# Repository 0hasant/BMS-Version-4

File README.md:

# Solar Team Solaris BMS Version 4

BQ76952-based BMS (up to 16S per board) with an STM32F103C8 host, isolated CAN,
external cell balancing and contactor control.

**System:** the 26S battery pack uses **two BMS boards**. Contactor coil current
is about 0.4 A. Balancing is enabled by an external button (J4 opto input).

**Active branch:** `v4.02` (the ordered board, Gerbers in `Hardware/All_Gerber/Gerber v4.02.zip`).

**Present focus:** make the firmware stable on the board that already works
(v4.013) before the v4.02 board arrives.

---

## Firmware (Software/BMSv4_Main_Code)

### Done
- [x] SPI driver with CRC check and retries on every frame (`bq76952.c`)
- [x] CONFIG_UPDATE wait checks the correct bit (Battery Status bit 0, `CFGUPDATE`)
- [x] All RAM settings written in one CONFIG_UPDATE session and read back to verify
- [x] BQ76952 reset detected (POR flag) and configuration re-applied automatically
- [x] MCU reset button (S2) also resets the BQ76952 (`BQ_RESET_ON_BOOT`)
- [x] Independent watchdog (IWDG, ~2 s, frozen while debugging)
- [x] Safety Status A/B/C, Battery Status and Alarm Status read every loop
- [x] Stack voltage as `uint32_t` (a full 16S pack is above 65.5 V)
- [x] Communication health counters in `BQ_Health` (watch in debugger)
- [x] Cell count selectable with `BMS_CELL_CONFIG` in `bq76952.h` (7 = 7S bench test, 13, 16).
      7S bench wiring: cells 1-7 on VC1-VC7, VC8..VC16 shorted to the top of cell 7 (`BMS_7S_TOP_ON_VC16 0`).
      Wiring check in the debugger: `BQ_Input_mV[16]` and `Stack_Diff_mV` (should be about 0)
- [x] CC Gain / Capacity Gain written from `BQ_SHUNT_MOHM`: current register is real mA (+/-32.7 A range).
      Calibrate by adjusting `BQ_SHUNT_MOHM` against a reference meter

### To do (on the working board)
- [ ] Protection setup: COV/CUV for the DMEGC INR45E cells, enable CUV, OCC/OCD1/OCD2/SCD
      thresholds for the 2 mOhm shunt (default SCD = 10 mV = only 5 A!), OTC/OTD
- [ ] Current: fine-tune `BQ_SHUNT_MOHM` with a current source, Board Offset (0x91C8) for the zero reading,
      10 mA user units if more than 32 A must be read
- [ ] Disable the charge pump (CP1 is tied to BAT, saves ~200 uA)
- [ ] Balancing: production `BALANCE_MIN_VOLTAGE_MV = 3900`, real temperature limits,
      `BALANCE_MAX_CELLS` chosen for heat (see Hardware notes)

### To do (for the v4.02 board, after it arrives)
- [ ] Fix `.ioc` before regenerating code:
  - PB10 = BMS number input (pull-down R31). PB11 = **contactor output** (rework below)
  - Mux select lines: PB15 = S0, PB14 = S1, PB13 = S2, PB12 = S3 (the `.ioc` has them reversed)
  - Remove PB8 output and I2C1 (PB8/PB7 are tied to SPI SCLK/MISO through R1/R2)
  - HSE = crystal (Y1, 16 MHz), not external clock; then 72 MHz SYSCLK
  - PA8 = balance-enable opto input (pull-up R30), PA0 = ADC for the thermistor mux
  - CAN at the bitrate used by the car
- [ ] Contactor logic on PB11: ON only when configured, no safety fault, SPI healthy;
      OFF on any fault. Watchdog reset -> pin floats -> R32 pulls it low -> contactor OFF
- [ ] 13S per board: set `BMS_CELL_CONFIG 13` (`0x8FFF`, unused VC13-VC15 shorted to VC12);
      board number from PB10
- [ ] Cell temperature reading through the CD74HC4067 mux
- [ ] CAN messages
- [ ] Balance-enable button (J4) with debounce

---

## Hardware

### v4.02 (ordered) - fixes before / during assembly
- [ ] **PS1:** fit **1S4E_0505S1U** (5 V in). The BOM part 1S4E_1505S1U is the 15 V input version -> CAN would be dead
- [ ] **F1:** 250 mA fuse blows when the top cell balances (~0.42 A). Use 1 A, 2410 size
      (e.g. Reomax SET1100 1 A 125 V time-lag, in stock at Özdisan). The 2410 body (6.1 mm) is
      longer than the 2010 footprint, solder carefully
- [ ] **Contactor drive (DDSG can't drive the PhotoMOS LEDs from REG18):**
  1. Bottom side: cut the short trace from the via in R10 pad 2 (89.5, 83.25) to the via at (95.25, 87.03)
  2. Wire SW1 pin 2 (PB11) to R28 pad 1 (R28/R29 LED node)
  3. Do **not** close SW1 position 1-2 (it would force the contactor on). Better: leave SW1 out and
     bridge pads 3-4 for BMS #2 (PB10 high)
  4. R10 can stay unfitted. Keep R32 (pull-down = contactor off during reset)
- [ ] **R1/R2:** leave unfitted (reserved for future I2C work)
- [ ] **VDDA:** add 100 nF + 1 uF from TP5 to GND (no decoupling on the board)
- [ ] **Ground, lower board (carries pack current through the shunt):** wire GND to TP2 (-Batt_In,
      battery side of the shunt) and **remove R43**. Never fit both, or pack current flows in the cell-0 sense wire
- [ ] **Ground, upper board (no pack current):** keep R43 = 0 R, tie TP2 and TP3 to GND so SRP/SRN do not float
- [x] Balance resistors changed to **22 R, 2 W, 2512** (HP122WJ0220T4E) in schematic and PCB: ~0.19 A and
      ~0.8 W each at 4.2 V (10 R was ~1.7 W each). Same footprint, BOM change only.
      Özdisan has it at 0 stock today (Request Price & Stock); any 22 R 2 W 2512 fits
- [ ] C27 (CAN split termination) is 10 pF, should be ~4.7 nF
- [x] BOM regenerated from the current schematic: `Hardware/BMS_V4/BOM/BMS_V4.02_BOM.xlsx` (and `.csv`), see below

### BOM
`Hardware/BMS_V4/BOM/BMS_V4.02_BOM.xlsx` - one line per part number, with Özdisan link, stock, price (TRY, tax
included, at MOQ, checked 2026-10-13) and a "Boards to build" cell that updates the quantities to buy. A second
table lists the off-board parts (mating plugs for J1-J5, jumpers for J7/J8). The `.csv` is the same list as plain text.
`Docs/Listeler/BMS_V4.013.xlsx` and `Hardware/BMS_V4/BMS_V4.csv` are old (v4.013 references), do not order from them.

Not in stock at Özdisan on 2026-10-13 (order elsewhere or "Request Price & Stock"): BQ76952 (U1), CD74HC4067 (U6),
BAT46W (D1), 22R 2W 2512 (balance resistors), NTC TH1-TH3, 10k 1% (R33), 0R (R43), 30pF (C24/C25, 47pF is in stock
if you want to change), 56pF (C33), 1206 caps C1 and C29, 3.3nF 2kV disc (C26), J5 header, J6 box header,
PS1 (not sold by Özdisan; RECOM RFM-0505S is a candidate, check pinout first). C35 (TDK 10uF 50V) has only 9 left.

### Component naming in the schematic
Every symbol now follows the same rule; the full part number is in hidden fields
(`MPN`, `Manufacturer`, `Supplier`, `Supplier Link`), visible in the symbol properties and in the BOM.

| Part type | Value shows | Example |
|---|---|---|
| Resistor | resistance, power only if >= 1 W, tolerance only where it matters | `4.7k`, `22R 2W`, `10k 1%` |
| Capacitor | capacitance + voltage | `100nF 50V`, `3.3nF 2kV` |
| Inductor / crystal / fuse | main value | `220uH`, `16MHz`, `1A slow` |
| IC, diode, transistor | short part name | `BQ76952`, `SI1050X`, `BAT54C` |
| Connector / switch | what it connects or does | `Cells 0-9`, `CAN`, `BMS ID`, `MCU reset` |

R1 and R2 are marked DNP (do not populate). The PCB Value fields were synced to the schematic
(this also fixes Q1-Q16, which showed RQ6E080AJ on the PCB).

Reference designators kept as they are on v4.02 so they match the ordered board's silkscreen.
For v4.03 rename: C36/C37 (PhotoMOS relays) -> K1/K2, LED1 -> D36, IC1/IC2 -> U7/U8.

### Next revision (v4.03) wish list
- [ ] Power REGIN from +5V_Main (BREG tied to REGIN, 1 uF at REGIN, 1 uF at REG1) and enable REG1 = 3.3 V:
      MISO becomes 3.3 V logic (`MISO_REG1` + SWAP_TO_SPI), and DDSG/DCHG can drive real loads.
      Not practical as a bodge on v4.02: pins 36/37 are tied to GND by traces that meet under the chip body
- [ ] **BQ reset button is wired wrong.** In the "bq76952 reset" block, R11 and C9 land on the S1 NO/GND side, so
      pressing S1 only shorts the R12 node (3.3 V via 4.7 k) to GND and RST_SHUT never goes high.
      Fix: +3.3V -> S1 -> R12 (1 k) -> RST_SHUT; RST_SHUT -> R11 (10 k, was 100 R) -> GND; C9 100 nF RST_SHUT -> GND.
      Short press = reset, held > 1 s = SHUTDOWN (the TS2 thermistor wakes it again). Optionally also an STM32 pin.
      On v4.02: use S2; the firmware sends RESET() to the BQ at every MCU boot
- [ ] Direct GND star point at the battery side of the shunt, VC0 through R/C to it
- [ ] Separate VC16 sense wire from the fused power wire (fuse drop shows up in cell 16)
- [ ] Balance-enable input: R27 sized for the button supply voltage (5 V needs ~1 k)
- [ ] Contactor wiring for two boards in series (flyback diode only once, across the coil)
- [ ] MOSI bottom link is a graphic line with a net; convert to a real track

---

## Repository organisation

- `main` is far behind `v4.02`: merge `v4.02` into `main` once the board is verified
- Remove `Hardware/BMS_V4/untitled.kicad_sch` (not in the hierarchy, old flat schematic)
- Lock files (`*.lck`), `fp-info-cache` and auto-save files are now ignored; don't commit them
- `Hardware/Porduciton Outputs/` -> rename to `Production Outputs`; `report.txt` still points to v4.013
- Keep one BOM file generated from the current schematic, next to the Gerbers of the same version
- Tag each ordered board, e.g. `hw-v4.02` on the commit the Gerbers came from

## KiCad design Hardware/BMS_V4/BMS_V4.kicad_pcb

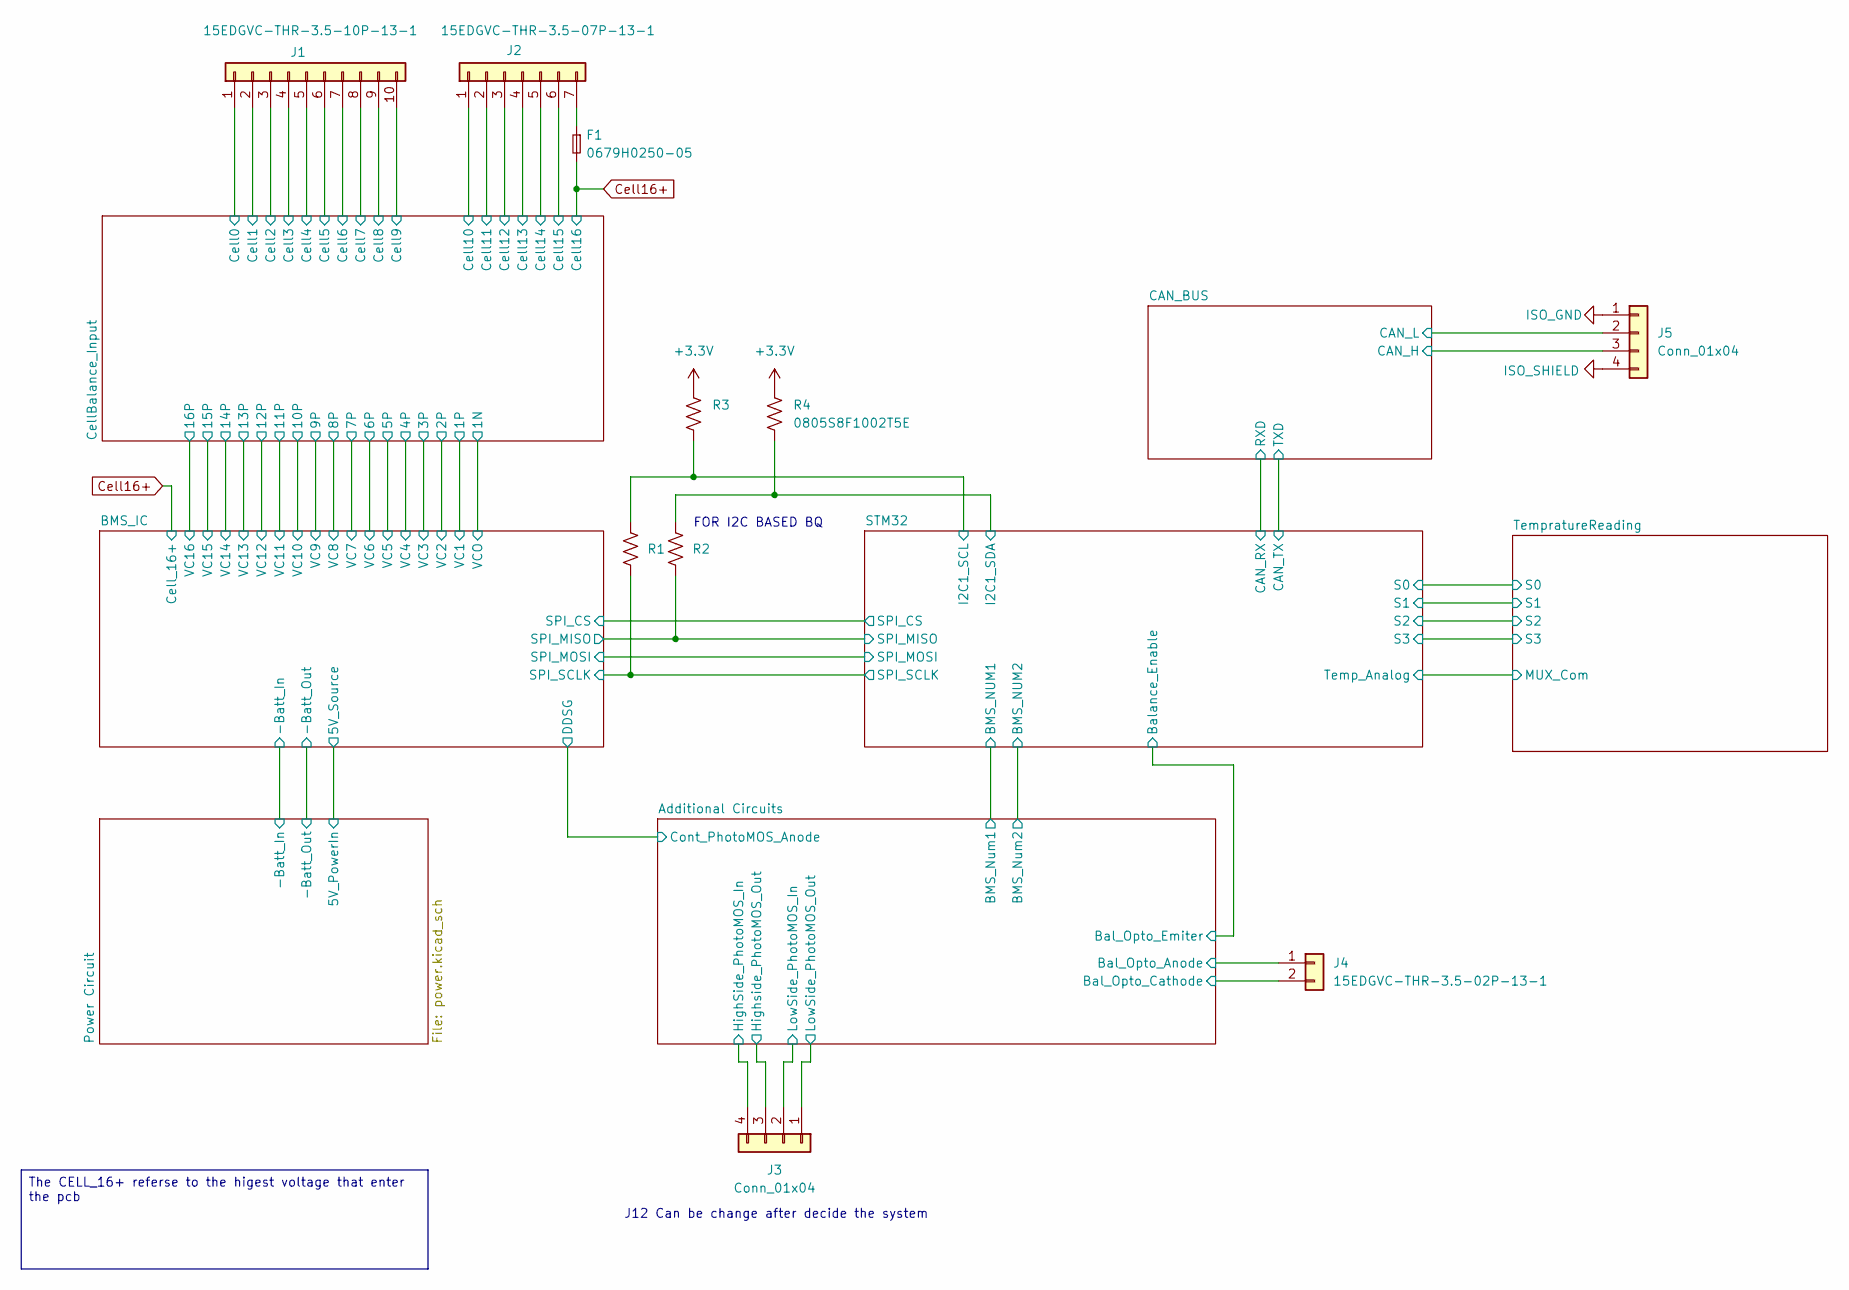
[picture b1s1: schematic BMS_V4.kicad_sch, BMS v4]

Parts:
F1: 0679H0250-05; Fuse_2010_5025Metric_Pad1.52x2.65mm_HandSolder
J1: 15EDGVC-THR-3.5-10P-13-1; PhoenixContact_MCV_1,5_10-G-3.5_1x10_P3.50mm_Vertical
J2: 15EDGVC-THR-3.5-07P-13-1; PhoenixContact_MCV_1,5_7-G-3.5_1x07_P3.50mm_Vertical
J3: Conn_01x04; Wago_734-134_1x04_P3.50mm_Vertical
J4: 15EDGVC-THR-3.5-02P-13-1; Wago_734-132_1x02_P3.50mm_Vertical
J5: Conn_01x04; PhoenixContact_MSTBVA_2,5_4-G-5,08_1x04_P5.08mm_Vertical
R1, R2: 0805S8F0000TDE; R_0805_2012Metric_Pad1.20x1.40mm_HandSolder
R3, R4: 0805S8F1002T5E; R_0805_2012Metric_Pad1.20x1.40mm_HandSolder

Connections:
+3.3V: R3.1, R4.2; also elsewhere on the board
/Additional Circuits/Bal_Opto_Anode: J4.1; also elsewhere on the board
/Additional Circuits/Bal_Opto_Cathode: J4.2; also elsewhere on the board
/Additional Circuits/HighSide_PhotoMOS_In: J3.4; also elsewhere on the board
/Additional Circuits/Highside_PhotoMOS_Out: J3.3; also elsewhere on the board
/Additional Circuits/LowSide_PhotoMOS_In: J3.2; also elsewhere on the board
/Additional Circuits/LowSide_PhotoMOS_Out: J3.1; also elsewhere on the board
/BMS_IC/SPI_MISO: R2.2; also elsewhere on the board
/BMS_IC/SPI_SCLK: R1.2; also elsewhere on the board
/CAN_BUS/CAN_H: J5.3; also elsewhere on the board
/CAN_BUS/CAN_L: J5.2; also elsewhere on the board
/CellBalance_Input/Cell0: J1.1; also elsewhere on the board
/CellBalance_Input/Cell1: J1.2; also elsewhere on the board
/CellBalance_Input/Cell2: J1.3; also elsewhere on the board
/CellBalance_Input/Cell3: J1.4; also elsewhere on the board
/CellBalance_Input/Cell4: J1.5; also elsewhere on the board
/CellBalance_Input/Cell5: J1.6; also elsewhere on the board
/CellBalance_Input/Cell6: J1.7; also elsewhere on the board
/CellBalance_Input/Cell7: J1.8; also elsewhere on the board
/CellBalance_Input/Cell8: J1.9; also elsewhere on the board
/CellBalance_Input/Cell9: J1.10; also elsewhere on the board
/CellBalance_Input/Cell10: J2.1; also elsewhere on the board
/CellBalance_Input/Cell11: J2.2; also elsewhere on the board
/CellBalance_Input/Cell12: J2.3; also elsewhere on the board
/CellBalance_Input/Cell13: J2.4; also elsewhere on the board
/CellBalance_Input/Cell14: J2.5; also elsewhere on the board
/CellBalance_Input/Cell15: J2.6; also elsewhere on the board
/STM32/I2C1_SCL: R1.1, R3.2; also elsewhere on the board
/STM32/I2C1_SDA: R2.1, R4.1; also elsewhere on the board
Cell16+: F1.2; also elsewhere on the board
ISO_GND: J5.1; also elsewhere on the board
ISO_SHIELD: J5.4; also elsewhere on the board
unnamed: F1.1, J2.7

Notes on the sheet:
J12 Can be change after decide the system
FOR I2C BASED BQ
The CELL_16+ referse to the higest voltage that enter the pcb

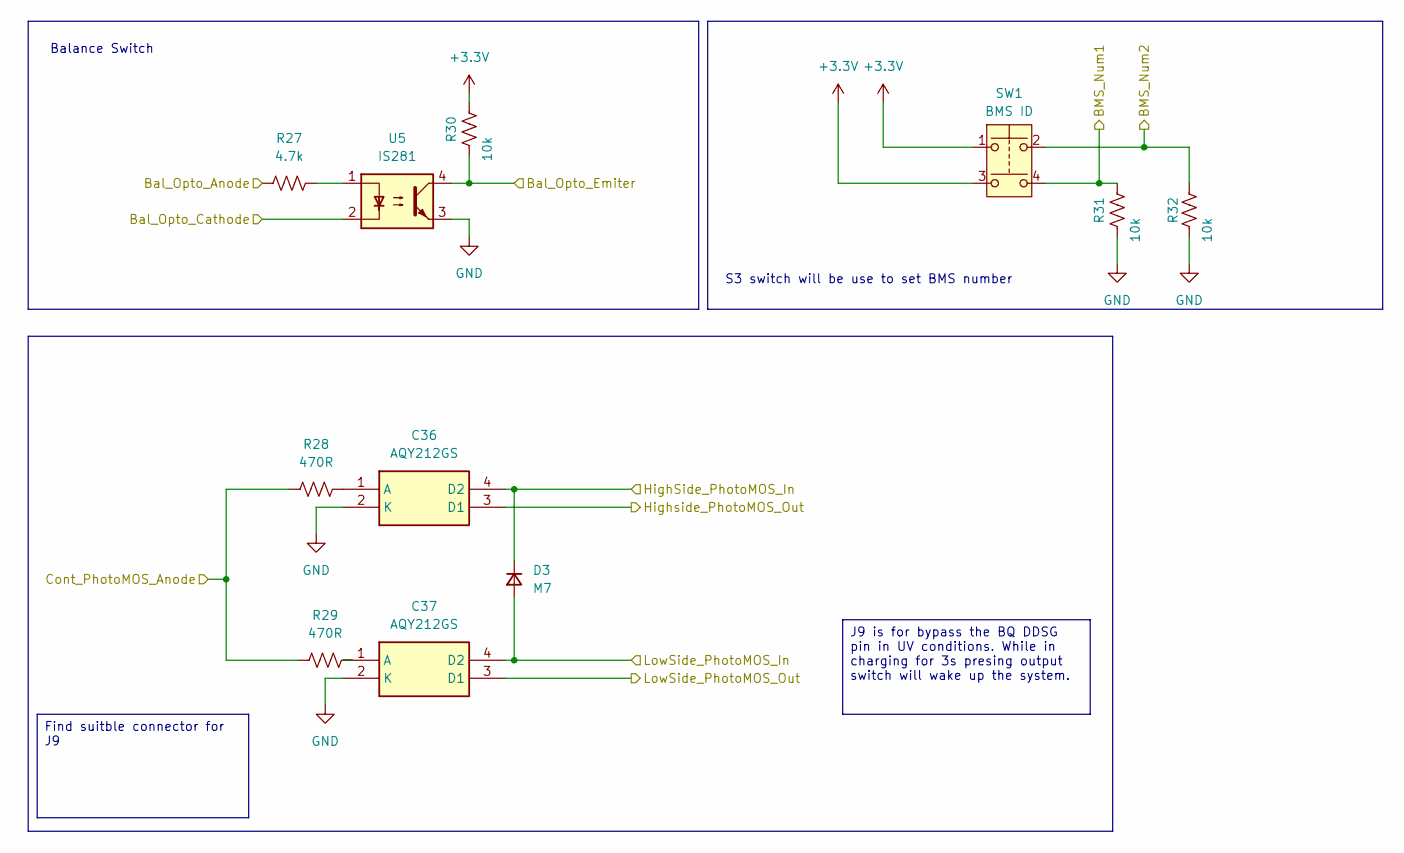
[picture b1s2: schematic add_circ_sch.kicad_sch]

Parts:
C36, C37: AQY212GS; SOP254P680X230-4N; MPN AQY212GSZ
D3: M7; D_SMA_Handsoldering; MPN M7-HT
R27: 4.7k; R_0805_2012Metric_Pad1.20x1.40mm_HandSolder; MPN CRT05F7E4701
R28, R29: 470R; R_0805_2012Metric_Pad1.20x1.40mm_HandSolder; MPN 0805S8F4700T5E
R30, R31, R32: 10k; R_0805_2012Metric_Pad1.20x1.40mm_HandSolder; MPN 0805S8J0103T5E
SW1: BMS ID; SW_DIP_SPSTx02_Slide_9.78x7.26mm_W7.62mm_P2.54mm; MPN NDS-02V
U5: IS281; SO-4_4.4x2.3mm_P1.27mm; MPN IS281GB

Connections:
+3.3V: R30.1, SW1.1, SW1.3; also elsewhere on the board
/Additional Circuits/BMS_Num1: R31.1, SW1.4; also elsewhere on the board
/Additional Circuits/BMS_Num2: R32.1, SW1.2; also elsewhere on the board
/Additional Circuits/Bal_Opto_Anode: R27.1; also elsewhere on the board
/Additional Circuits/Bal_Opto_Cathode: U5.2; also elsewhere on the board
/Additional Circuits/Bal_Opto_Emiter: R30.2, U5.4; also elsewhere on the board
/Additional Circuits/Cont_PhotoMOS_Anode: R28.1, R29.1; also elsewhere on the board
/Additional Circuits/HighSide_PhotoMOS_In: C36.4 (D2), D3.1 (K); also elsewhere on the board
/Additional Circuits/Highside_PhotoMOS_Out: C36.3 (D1); also elsewhere on the board
/Additional Circuits/LowSide_PhotoMOS_In: C37.4 (D2), D3.2 (A); also elsewhere on the board
/Additional Circuits/LowSide_PhotoMOS_Out: C37.3 (D1); also elsewhere on the board
GND: C36.2 (K), C37.2 (K), R31.2, R32.2, U5.3; also elsewhere on the board
unnamed: C36.1 (A), R28.2
unnamed: C37.1 (A), R29.2
unnamed: R27.2, U5.1

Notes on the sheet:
S3 switch will be use to set BMS number
Balance Switch
J9 is for bypass the BQ DDSG pin in UV conditions. While in charging for 3s presing output switch will wake up the system.
Find suitble connector for J9

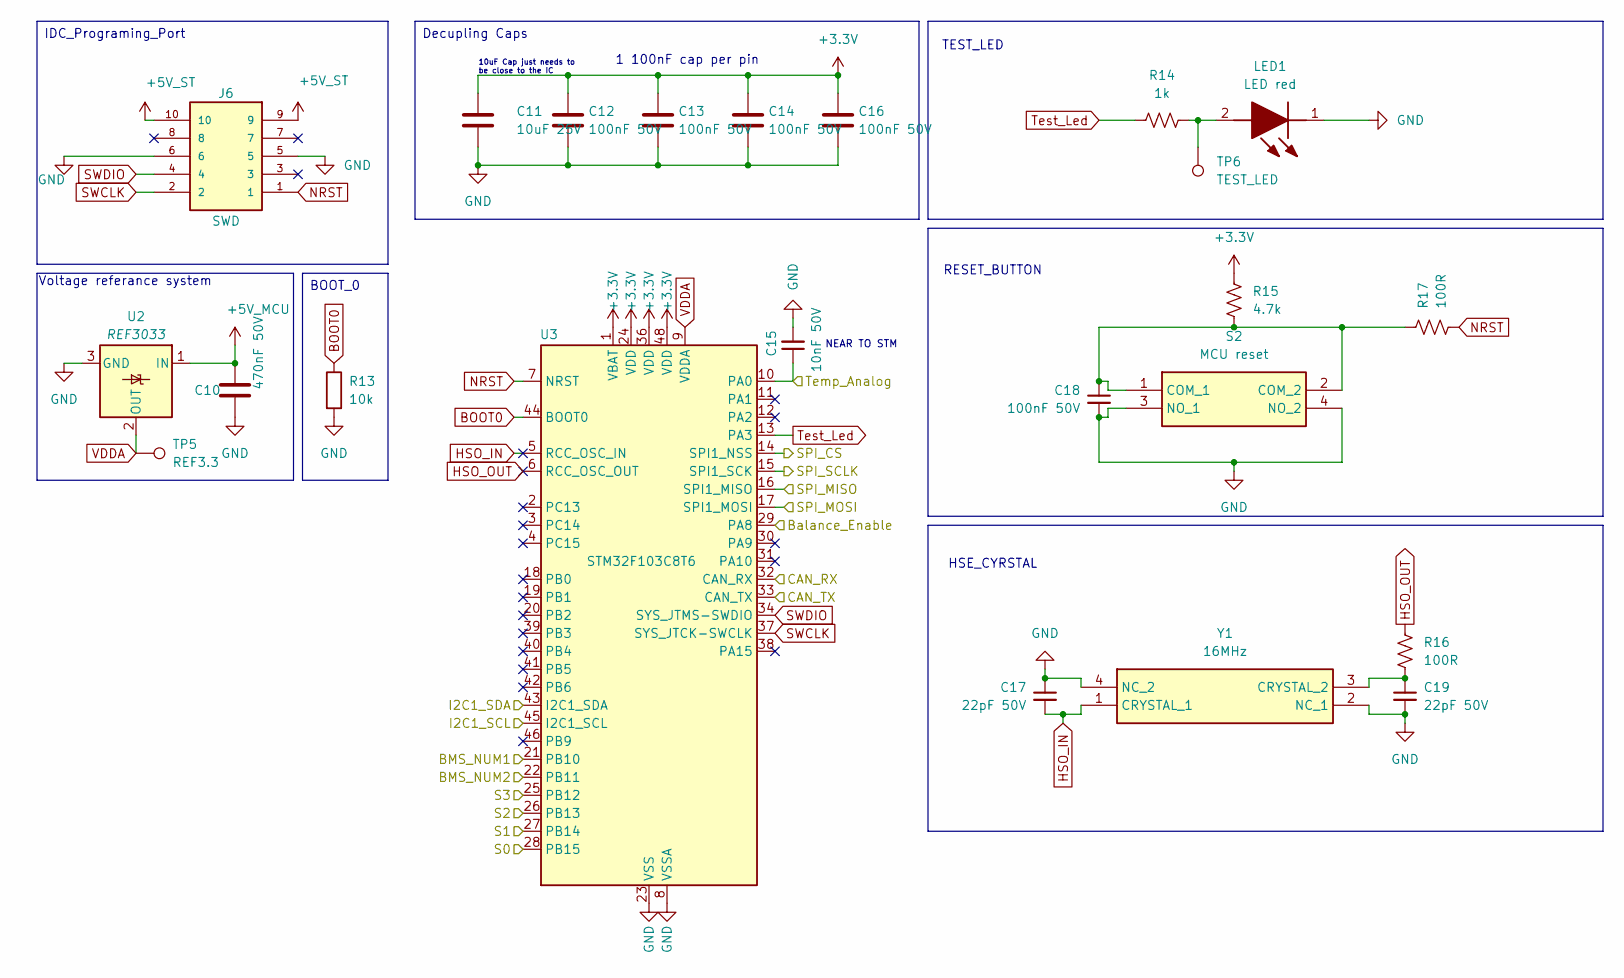
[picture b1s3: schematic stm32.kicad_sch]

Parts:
C10: 470nF 50V; C_0805_2012Metric_Pad1.18x1.45mm_HandSolder; MPN CL21B474KBFNNNE
C11: 10uF 25V; C_0805_2012Metric_Pad1.18x1.45mm_HandSolder; MPN GRT21BC71E106KE13L
C12, C13, C14, C16, C18: 100nF 50V; C_0805_2012Metric_Pad1.18x1.45mm_HandSolder; MPN CL21B104KBCNNNC
C15: 10nF 50V; C_0805_2012Metric_Pad1.18x1.45mm_HandSolder; MPN CL21B103KBANNNC
C17, C19: 22pF 50V; CAPC2012X94N; MPN CL21C220JBANNNC
J6: SWD; IDC-Header_2x05_P2.54mm_Vertical; MPN DS1013-10SSIB1
LED1: LED red; LEDC2012X110N; MPN KP-2012SRC-PRV; Mouser Part Number N/A
R13: 10k; R_0805_2012Metric_Pad1.20x1.40mm_HandSolder; MPN 0805S8J0103T5E
R14: 1k; RESC2012X70N; MPN 0805S8F1001T5E
R15: 4.7k; R_0805_2012Metric_Pad1.20x1.40mm_HandSolder; MPN CRT05F7E4701
R16: 100R; RES_ERA6AHD330V; MPN 0805S8F1000T5E
R17: 100R; R_0805_2012Metric_Pad1.20x1.40mm_HandSolder; MPN 0805S8F1000T5E
S2: MCU reset; DTS62RV; MPN DTS-62R-V; Mouser Part Number 113-DTS62RV
TP5: REF3.3; TestPoint_THTPad_D1.0mm_Drill0.5mm
TP6: TEST_LED; TestPoint_THTPad_D1.0mm_Drill0.5mm
U2: REF3033; SOT-23; MPN REF3033AIDBZR
U3: STM32F103C8T6; LQFP-48_7x7mm_P0.5mm; MPN STM32F103C8T6
Y1: 16MHz; RH10016000183050TR; MPN RH100-16.000-18-2030-EXT

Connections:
+3.3V: C11.1, C12.1, C13.1, C14.1, C16.1, R15.2, U3.1 (VBAT), U3.24 (VDD), U3.36 (VDD), U3.48 (VDD); also elsewhere on the board
+5V_MCU: C10.1, U2.1 (IN); also elsewhere on the board
+5V_ST: J6.9, J6.10; also elsewhere on the board
/Additional Circuits/BMS_Num1: U3.21 (PB10); also elsewhere on the board
/Additional Circuits/BMS_Num2: U3.22 (PB11); also elsewhere on the board
/Additional Circuits/Bal_Opto_Emiter: U3.29 (PA8); also elsewhere on the board
/BMS_IC/SPI_CS: U3.14 (SPI1_NSS); also elsewhere on the board
/BMS_IC/SPI_MISO: U3.16 (SPI1_MISO); also elsewhere on the board
/BMS_IC/SPI_MOSI: U3.17 (SPI1_MOSI); also elsewhere on the board
/BMS_IC/SPI_SCLK: U3.15 (SPI1_SCK); also elsewhere on the board
/CAN_BUS/RXD: U3.32 (CAN_RX); also elsewhere on the board
/CAN_BUS/TXD: U3.33 (CAN_TX); also elsewhere on the board
/STM32/I2C1_SCL: U3.45 (I2C1_SCL); also elsewhere on the board
/STM32/I2C1_SDA: U3.43 (I2C1_SDA); also elsewhere on the board
/STM32/S0: U3.28 (PB15); also elsewhere on the board
/STM32/S1: U3.27 (PB14); also elsewhere on the board
/STM32/S2: U3.26 (PB13); also elsewhere on the board
/STM32/S3: U3.25 (PB12); also elsewhere on the board
/STM32/Temp_Analog: C15.1, U3.10 (PA0); also elsewhere on the board
BOOT0: R13.1, U3.44 (BOOT0)
GND: C10.2, C11.2, C12.2, C13.2, C14.2, C15.2, C16.2, C17.1, C18.2, C19.2, J6.5, J6.6, LED1.1 (K), R13.2, S2.3 (NO_1), S2.4 (NO_2), U2.3 (GND), U3.8 (VSSA), U3.23 (VSS), U3.35 (VSS), U3.47 (VSS), Y1.2 (NC_1), Y1.4 (NC_2); also elsewhere on the board
HSO_IN: C17.2, U3.5 (RCC_OSC_IN), Y1.1 (CRYSTAL_1)
HSO_OUT: R16.1, U3.6 (RCC_OSC_OUT)
NRST: J6.1, R17.1, U3.7 (NRST)
unnamed: LED1.2 (A), R14.2, TP6.1 (1_1)
unnamed: C18.1, R15.1, R17.2, S2.1 (COM_1), S2.2 (COM_2)
unnamed: C19.1, R16.2, Y1.3 (CRYSTAL_2)
SWCLK: J6.2, U3.37 (SYS_JTCK-SWCLK)
SWDIO: J6.4, U3.34 (SYS_JTMS-SWDIO)
Test_Led: R14.1, U3.13 (PA3)
VDDA: TP5.1 (1_1), U2.2 (OUT), U3.9 (VDDA)

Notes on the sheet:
NEAR TO STM
HSE_CYRSTAL
TEST_LED
1 100nF cap per pin
Voltage referance system
RESET_BUTTON
10uF Cap just needs to be close to the IC
BOOT_0
IDC_Programing_Port
Decupling Caps

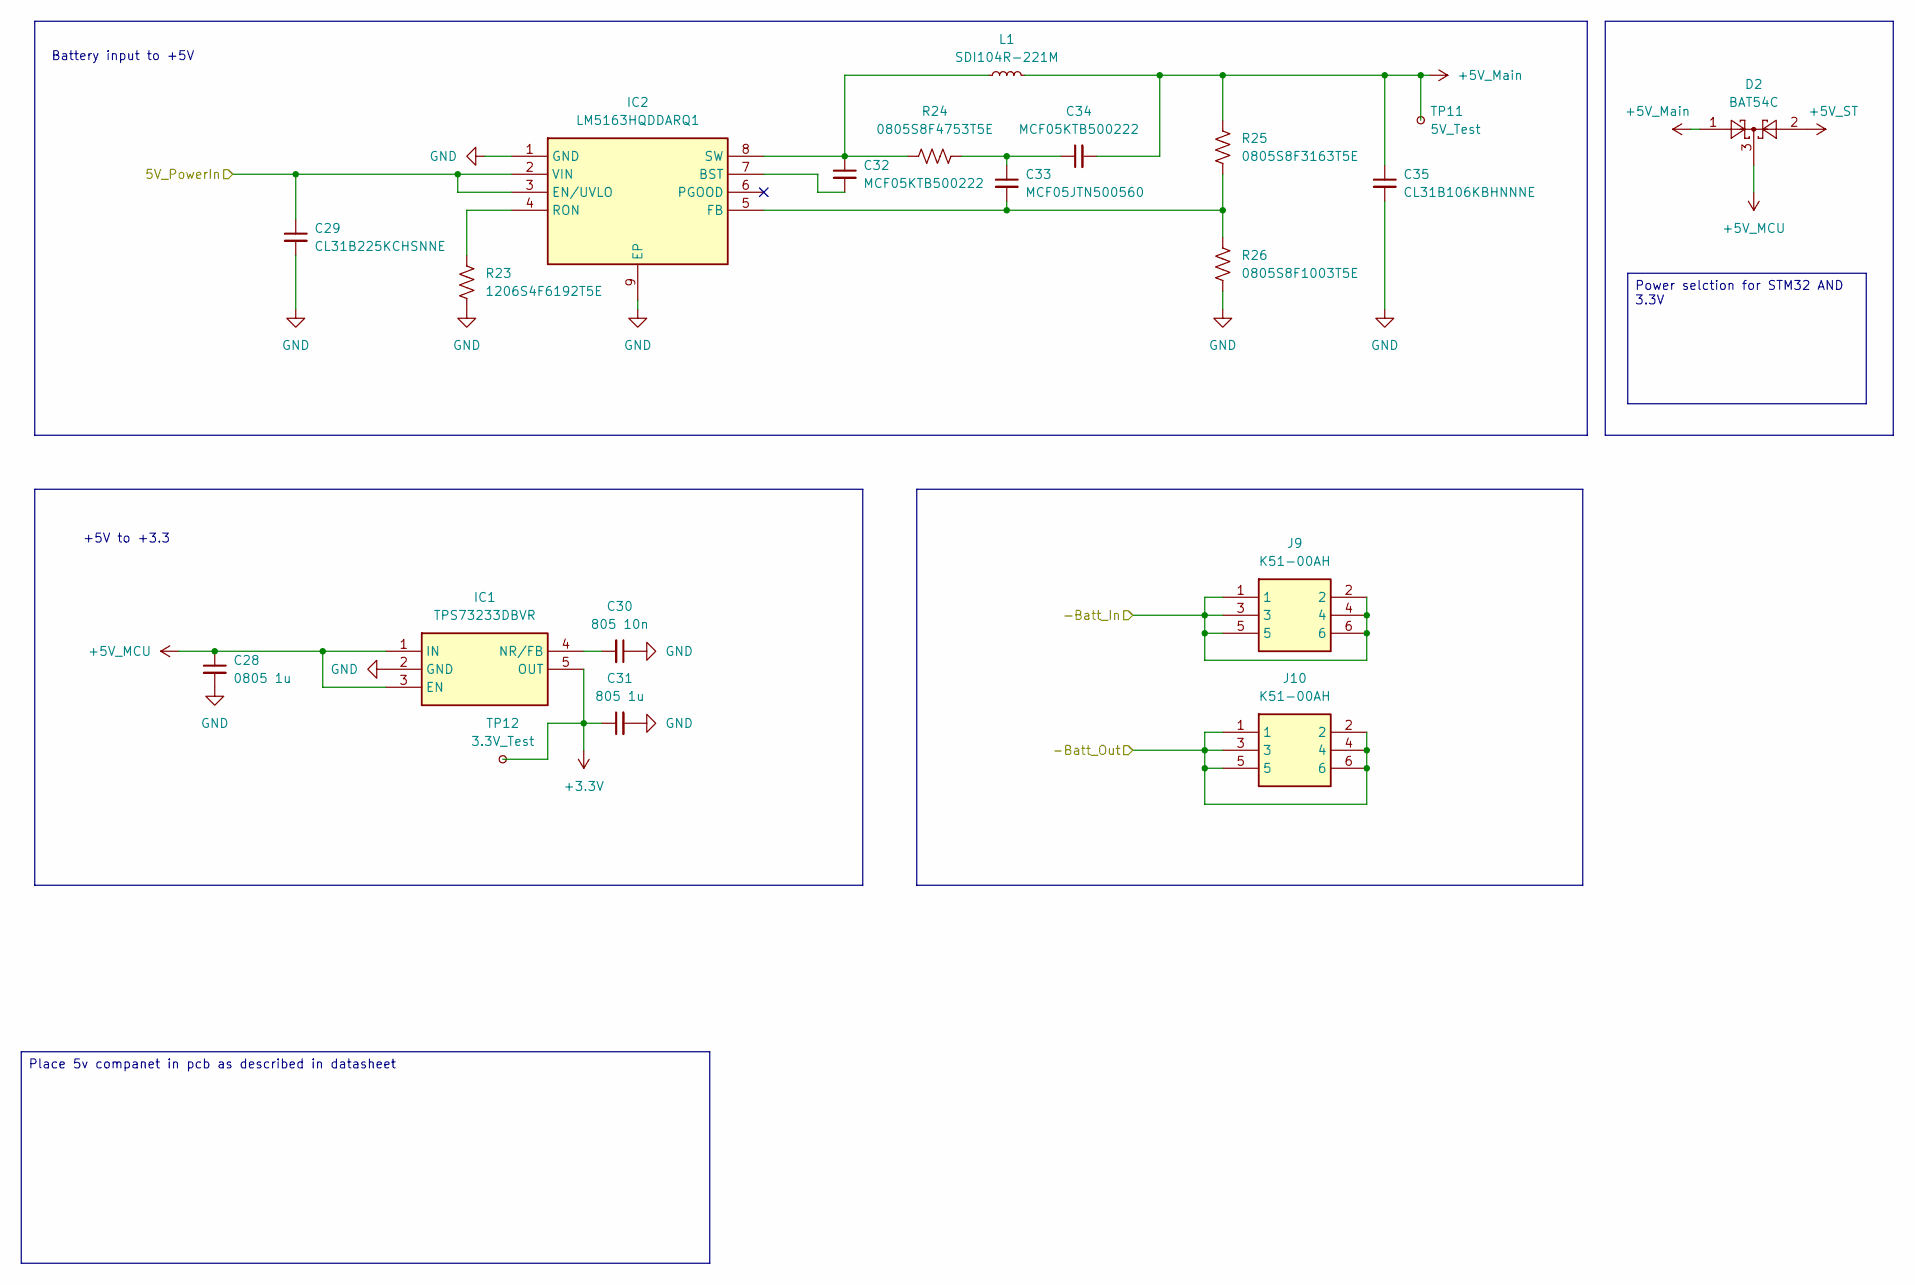
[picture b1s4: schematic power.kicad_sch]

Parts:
C28: 0805 1u; CAPC2012X94N
C29: CL31B225KCHSNNE; C_1206_3216Metric_Pad1.33x1.80mm_HandSolder
C30: 805 10n; CAPC2012X94N
C31: 805 1u; CAPC2012X94N
C32, C34: MCF05KTB500222; C_0805_2012Metric_Pad1.18x1.45mm_HandSolder
C33: MCF05JTN500560; C_0805_2012Metric_Pad1.18x1.45mm_HandSolder
C35: CL31B106KBHNNNE; C_1206_3216Metric_Pad1.33x1.80mm_HandSolder
D2: BAT54C; SOT-23
IC1: TPS73233DBVR; SOT95P280X145-5N; Manufacturer_Part_Number TPS73233DBVR; Mouser Part Number 595-TPS73233DBVR
IC2: LM5163HQDDARQ1; SOIC127P600X170-9N; Manufacturer_Part_Number LM5163HQDDARQ1; Mouser Part Number 595-LM5163HQDDARQ1
J9, J10: K51-00AH; K5100AH; Manufacturer_Part_Number K51-00A(H)
L1: SDI104R-221M; L_10.4x10.4_H4.8
R23: 1206S4F6192T5E; R_1206_3216Metric_Pad1.30x1.75mm_HandSolder
R24: 0805S8F4753T5E; R_0805_2012Metric_Pad1.20x1.40mm_HandSolder
R25: 0805S8F3163T5E; R_0805_2012Metric_Pad1.20x1.40mm_HandSolder
R26: 0805S8F1003T5E; R_0805_2012Metric_Pad1.20x1.40mm_HandSolder
TP11: 5V_Test; TestPoint_THTPad_1.5x1.5mm_Drill0.7mm
TP12: 3.3V_Test; TestPoint_THTPad_1.5x1.5mm_Drill0.7mm

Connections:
+3.3V: C31.1, IC1.5 (OUT), TP12.1; also elsewhere on the board
+5V_MCU: C28.1, D2.3, IC1.1 (IN), IC1.3 (EN); also elsewhere on the board
+5V_Main: C34.2, C35.1, D2.1, L1.2, R25.1, TP11.1; also elsewhere on the board
+5V_ST: D2.2; also elsewhere on the board
/BMS_IC/5V_Source: C29.1, IC2.2 (VIN), IC2.3 (EN/UVLO); also elsewhere on the board
/BMS_IC/-Batt_In: J9.1, J9.2, J9.3, J9.4, J9.5, J9.6; also elsewhere on the board
/BMS_IC/-Batt_Out: J10.1, J10.2, J10.3, J10.4, J10.5, J10.6; also elsewhere on the board
GND: C28.2, C29.2, C30.1, C31.2, C35.2, IC1.2 (GND), IC2.1 (GND), IC2.9 (EP), R23.2, R26.2; also elsewhere on the board
unnamed: C33.1, C34.1, R24.2
unnamed: C30.2, IC1.4 (NR/FB)
unnamed: C32.2, IC2.7 (BST)
unnamed: C33.2, IC2.5 (FB), R25.2, R26.1
unnamed: IC2.4 (RON), R23.1
unnamed: C32.1, IC2.8 (SW), L1.1, R24.1

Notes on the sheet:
+5V to +3.3
Battery input to +5V
Place 5v companet in pcb as described in datasheet
Power selction for STM32 AND 3.3V

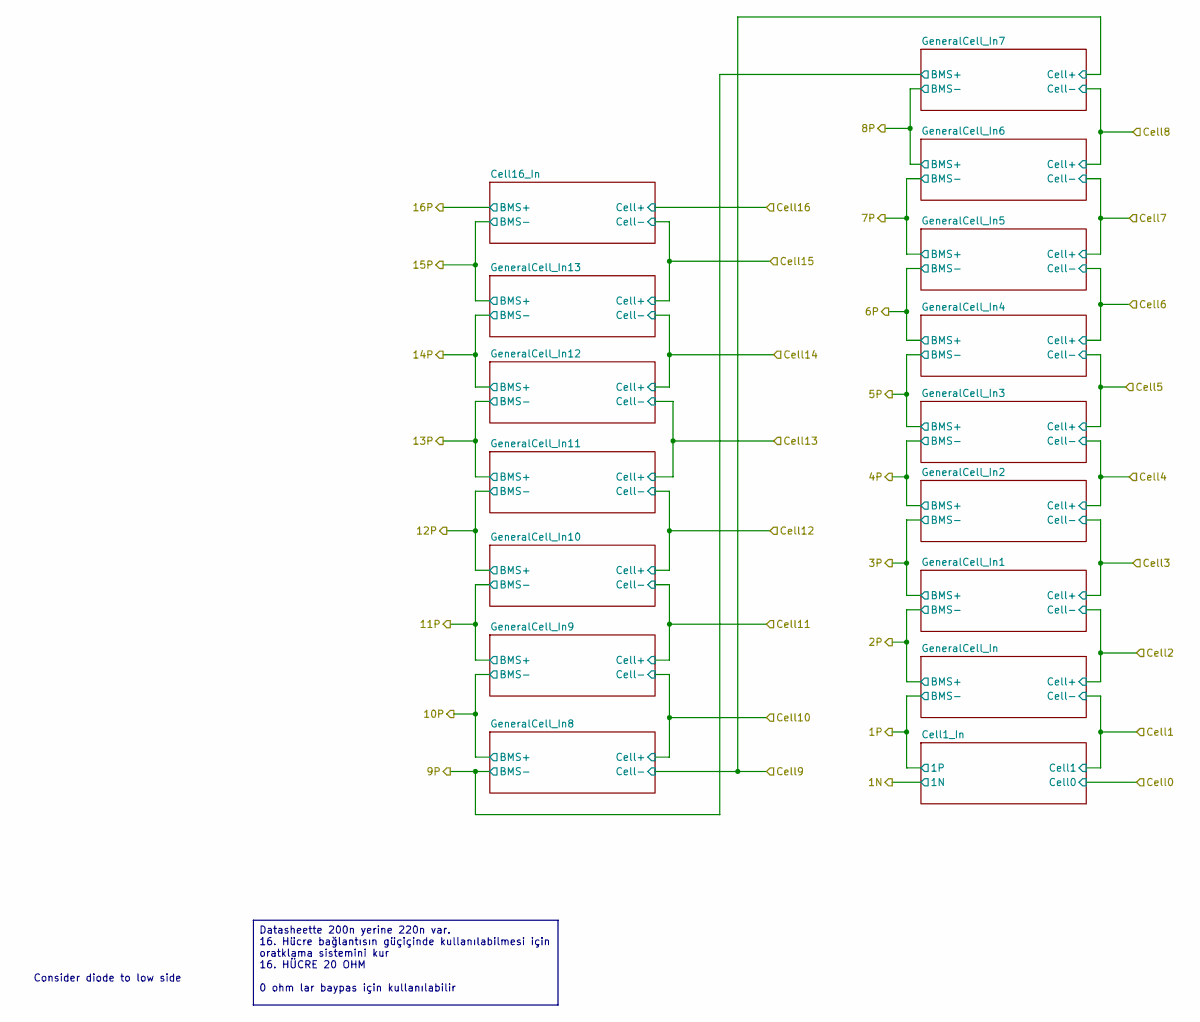
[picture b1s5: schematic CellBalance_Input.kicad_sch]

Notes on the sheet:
Consider diode to low side
Datasheette 200n yerine 220n var. 16. Hücre bağlantısın güçiçinde kullanılabilmesi için oratklama sistemini kur 16. HÜCRE 20 OHM 0 ohm lar baypas için kullanılabilir

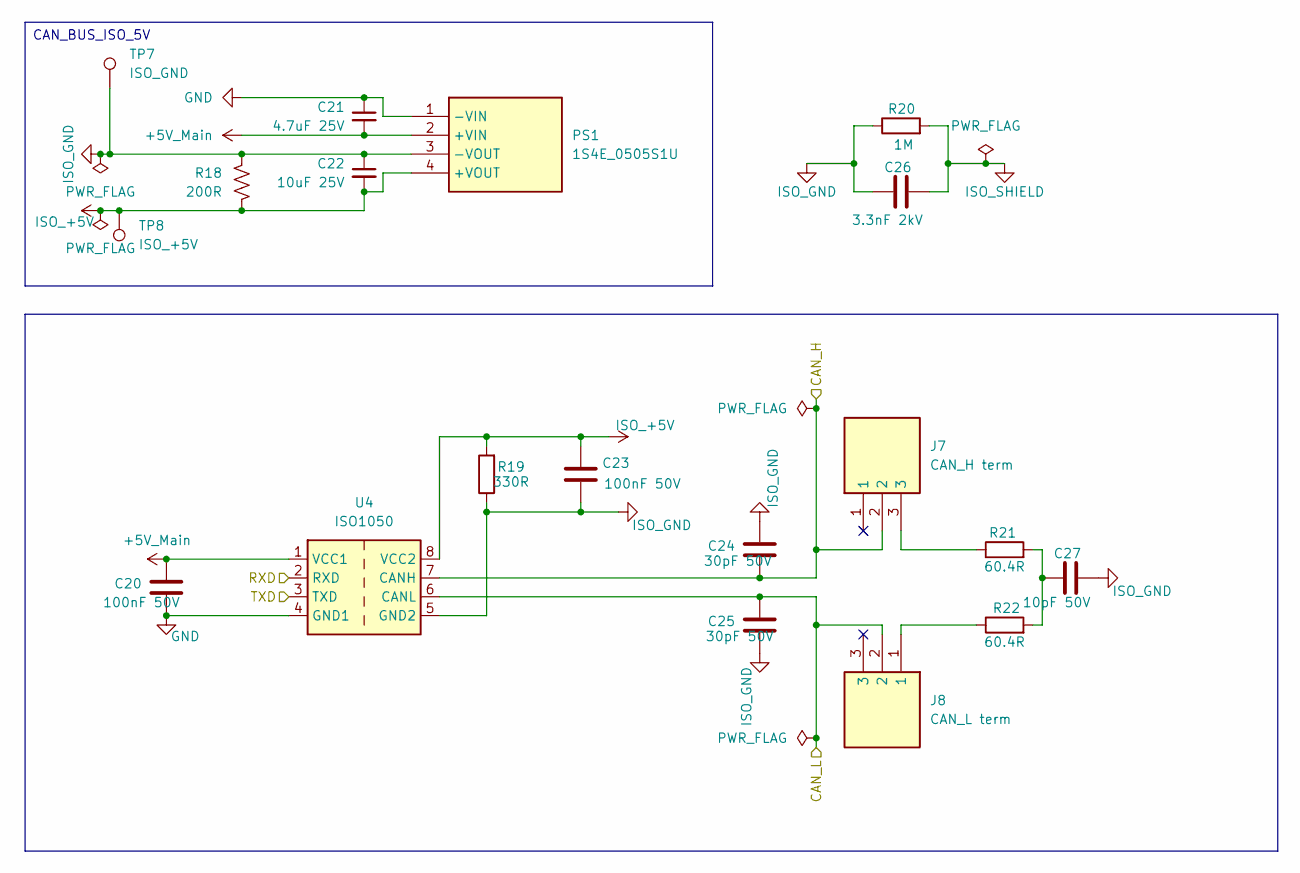
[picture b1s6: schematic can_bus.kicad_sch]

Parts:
C20, C23: 100nF 50V; C_0805_2012Metric_Pad1.18x1.45mm_HandSolder; MPN CL21B104KBCNNNC
C21: 4.7uF 25V; CAPC2012X94N; MPN CL21A475KAQNNNE
C22: 10uF 25V; CAPC2012X94N; MPN GRT21BC71E106KE13L
C24, C25: 30pF 50V; C_0805_2012Metric_Pad1.18x1.45mm_HandSolder; MPN CL21C300JBANNNC
C26: 3.3nF 2kV; C_Disc_D10.5mm_W5.0mm_P5.00mm; MPN KB3D332KL518Y
C27: 10pF 50V; C_0805_2012Metric_Pad1.18x1.45mm_HandSolder; MPN CC0805JRNPO9BN100
J7: CAN_H term; HDRV3W51P0X254_1X3_762X254X470P; MPN L-KLS1-207-1-40-S; Mouser Part Number 575-3801010300002000
J8: CAN_L term; HDRV3W51P0X254_1X3_762X254X470P; MPN L-KLS1-207-1-40-S; Mouser Part Number 575-3801010300002000
PS1: 1S4E_0505S1U; 1S4E_0303S1U; MPN 1S4E_0505S1U
R18: 200R; LED_0805_2012Metric_Pad1.15x1.40mm_HandSolder; MPN 0805S8F2000T5E
R19: 330R; R_0805_2012Metric_Pad1.20x1.40mm_HandSolder; MPN 0805S8F3300T5E
R20: 1M; R_0805_2012Metric_Pad1.20x1.40mm_HandSolder; MPN 0805S8F1004T5E
R21, R22: 60.4R; R_0805_2012Metric_Pad1.20x1.40mm_HandSolder; MPN 0805S8F604JT5E
TP7: ISO_GND; TestPoint_THTPad_D1.0mm_Drill0.5mm
TP8: ISO_+5V; TestPoint_THTPad_D1.0mm_Drill0.5mm
U4: ISO1050; SOP-8_6.62x9.15mm_P2.54mm; MPN ISO1050DUBR

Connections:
+5V_Main: C20.1, C21.2, PS1.2 (+VIN), U4.1 (VCC1); also elsewhere on the board
/CAN_BUS/CAN_H: C24.2, J7.2, U4.7 (CANH); also elsewhere on the board
/CAN_BUS/CAN_L: C25.1, J8.2, U4.6 (CANL); also elsewhere on the board
/CAN_BUS/RXD: U4.2 (RXD); also elsewhere on the board
/CAN_BUS/TXD: U4.3 (TXD); also elsewhere on the board
GND: C20.2, C21.1, PS1.1 (-VIN), U4.4 (GND1); also elsewhere on the board
ISO_+5V: C22.2, C23.1, PS1.4 (+VOUT), R18.2, R19.2, TP8.1 (1_1), U4.8 (VCC2)
ISO_GND: C22.1, C23.2, C24.1, C25.2, C26.1, C27.2, PS1.3 (-VOUT), R18.1, R19.1, R20.1, TP7.1 (1_1), U4.5 (GND2); also elsewhere on the board
ISO_SHIELD: C26.2, R20.2; also elsewhere on the board
unnamed: C27.1, R21.2, R22.2
unnamed: J7.3, R21.1
unnamed: J8.1, R22.1

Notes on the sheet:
CAN_BUS_ISO_5V

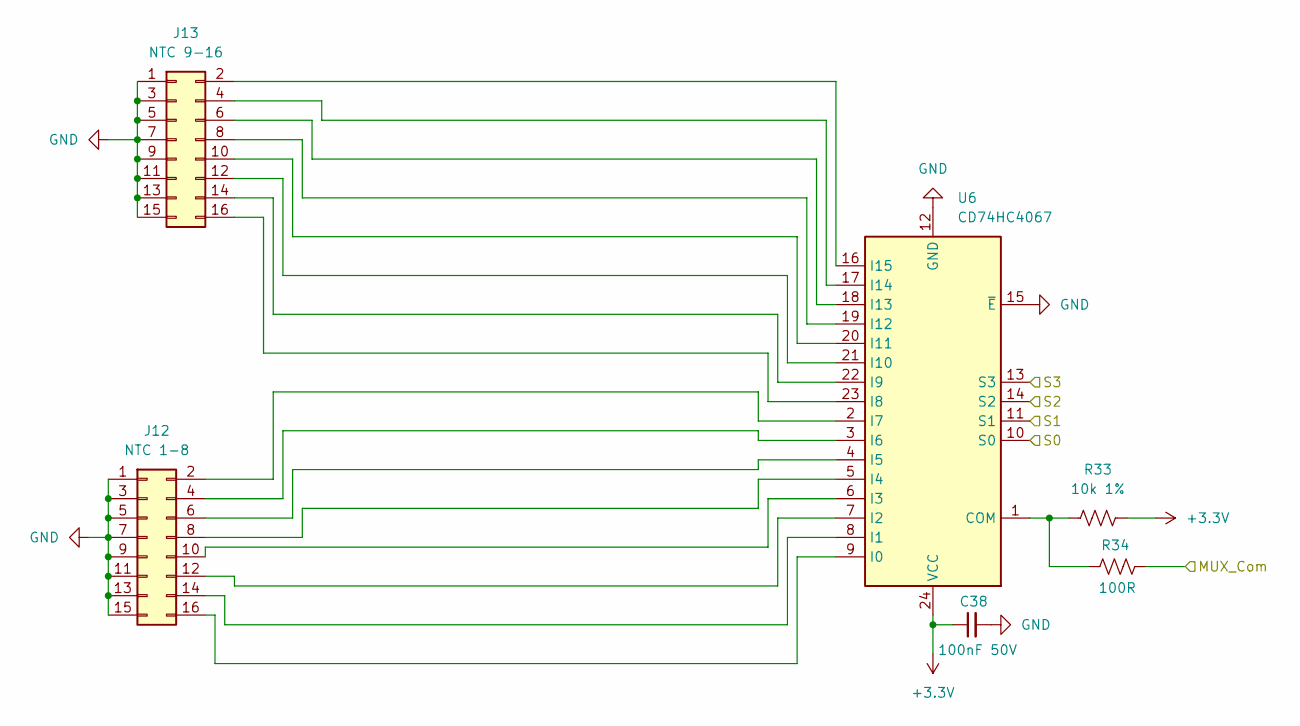
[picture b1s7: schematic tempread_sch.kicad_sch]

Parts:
C38: 100nF 50V; C_0805_2012Metric_Pad1.18x1.45mm_HandSolder; MPN CL21B104KBCNNNC
J12: NTC 1-8; PinSocket_2x08_P2.00mm_Vertical; MPN L-KLS1-XL4-2.00-2X08-S
J13: NTC 9-16; PinSocket_2x08_P2.00mm_Vertical; MPN L-KLS1-XL4-2.00-2X08-S
R33: 10k 1%; R_0805_2012Metric_Pad1.20x1.40mm_HandSolder; MPN 0805S8F1002T5E
R34: 100R; R_0805_2012Metric_Pad1.20x1.40mm_HandSolder; MPN 0805S8F1000T5E
U6: CD74HC4067; SSOP-24_5.3x8.2mm_P0.65mm; MPN CD74HC4067SM96

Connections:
+3.3V: C38.1, R33.2, U6.24 (VCC); also elsewhere on the board
/STM32/S0: U6.10 (S0); also elsewhere on the board
/STM32/S1: U6.11 (S1); also elsewhere on the board
/STM32/S2: U6.14 (S2); also elsewhere on the board
/STM32/S3: U6.13 (S3); also elsewhere on the board
/STM32/Temp_Analog: R34.2; also elsewhere on the board
GND: C38.2, J12.1, J12.3, J12.5, J12.7, J12.9, J12.11, J12.13, J12.15, J13.1, J13.3, J13.5, J13.7, J13.9, J13.11, J13.13, J13.15, U6.12 (GND), U6.15 (~E); also elsewhere on the board
unnamed: J12.2, U6.2 (I7)
unnamed: J12.4, U6.3 (I6)
unnamed: J12.6, U6.4 (I5)
unnamed: J12.8, U6.5 (I4)
unnamed: J12.10, U6.6 (I3)
unnamed: J12.12, U6.7 (I2)
unnamed: J12.14, U6.8 (I1)
unnamed: J12.16, U6.9 (I0)
unnamed: J13.2, U6.16 (I15)
unnamed: J13.4, U6.17 (I14)
unnamed: J13.6, U6.18 (I13)
unnamed: J13.8, U6.19 (I12)
unnamed: J13.10, U6.20 (I11)
unnamed: J13.12, U6.21 (I10)
unnamed: J13.14, U6.22 (I9)
unnamed: J13.16, U6.23 (I8)
unnamed: R33.1, R34.1, U6.1 (COM)
